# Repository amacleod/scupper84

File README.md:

Scupper84 Row-Staggered Wee Keyboard
=====================================

The Scupper84 is an 84-key (75% layout) row-staggered keyboard in CFX
spacing to be small. The name Scupper is a reference to the Stan
Rogers song [Barrett's Privateers][barretts] which contains the lyric,
"and the cook in the scuppers with the staggers and jags," since this
keyboard uses a row-staggered design.

[barretts]: https://en.wikipedia.org/wiki/Barrett%27s_Privateers

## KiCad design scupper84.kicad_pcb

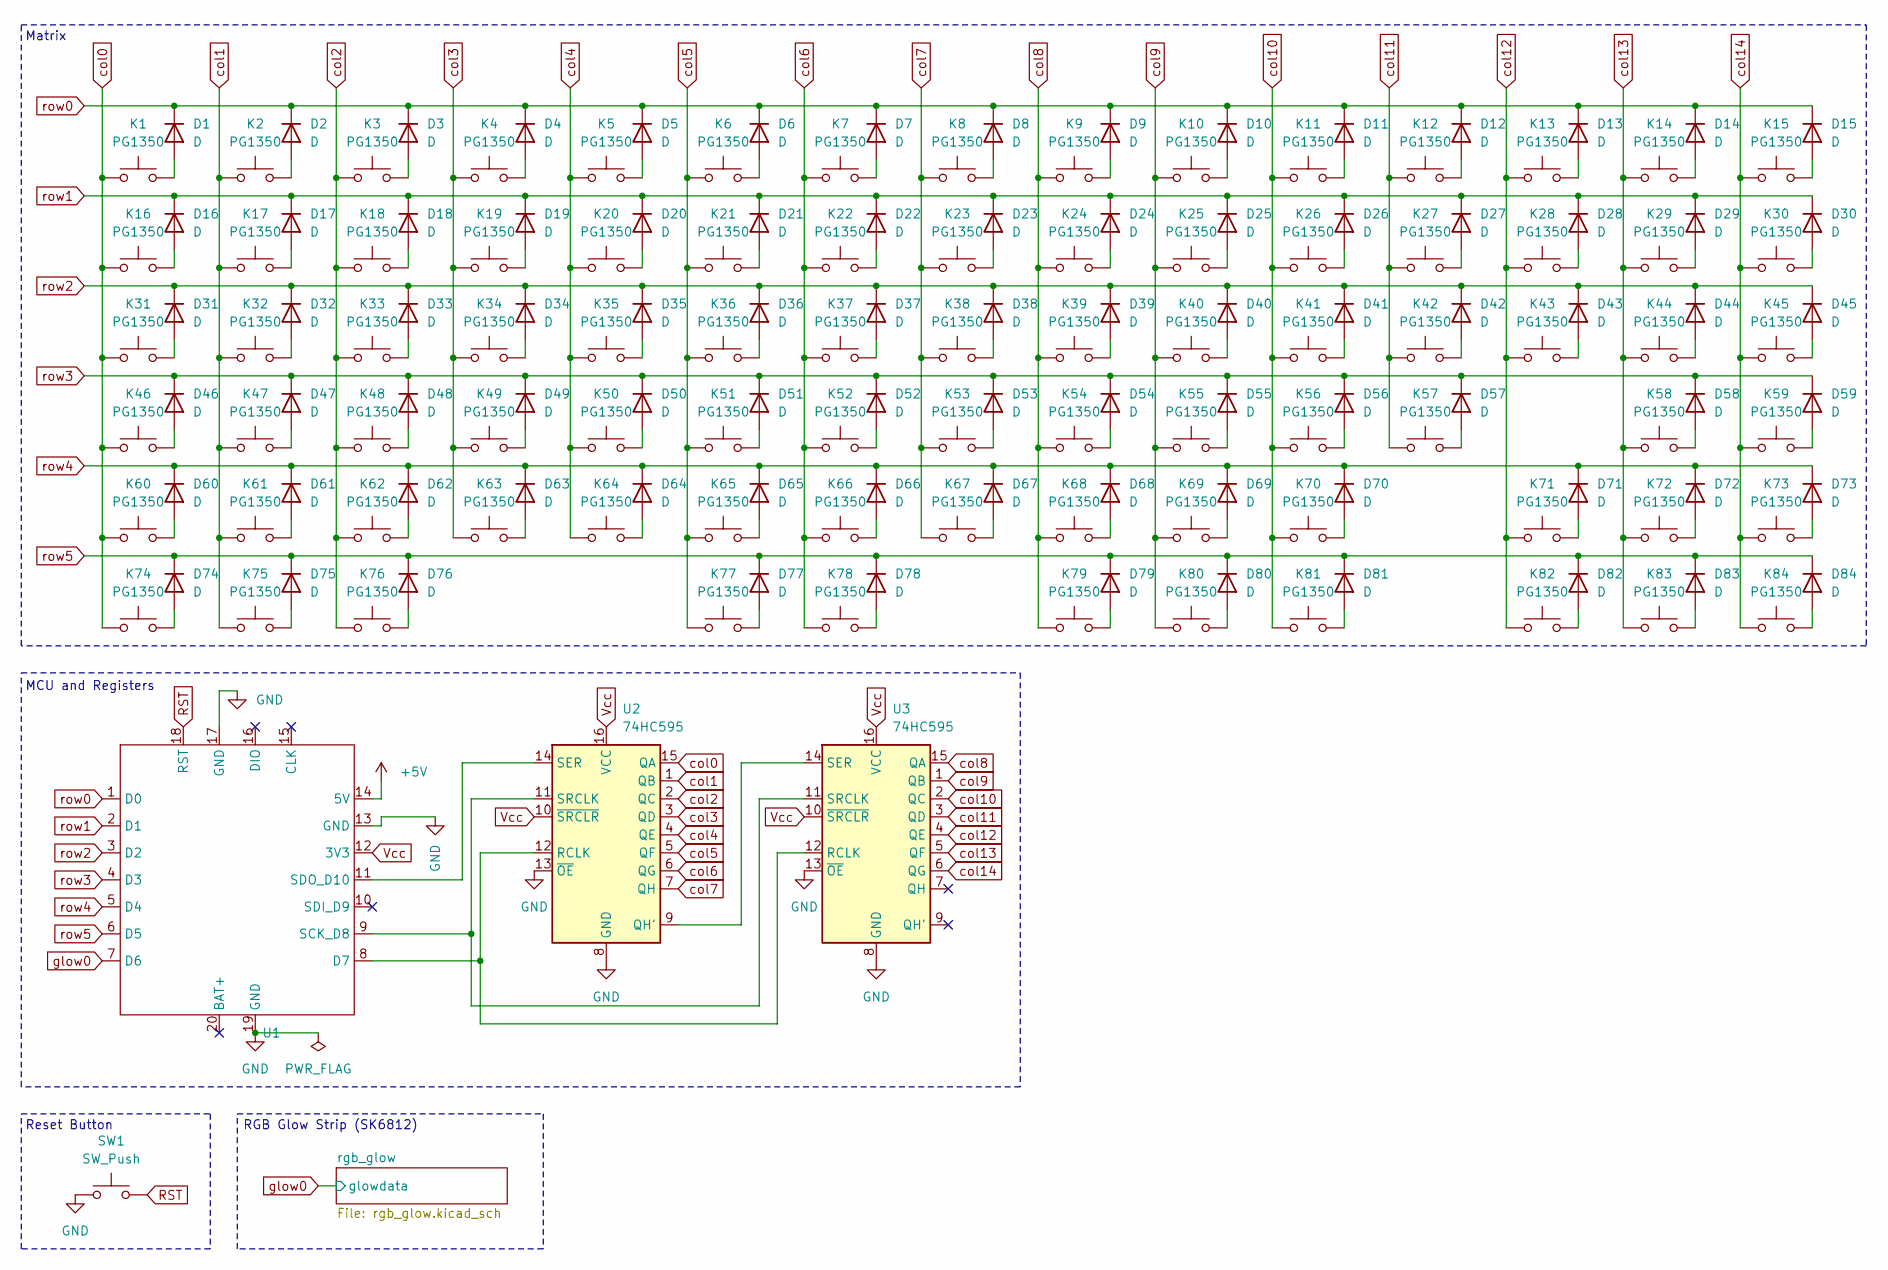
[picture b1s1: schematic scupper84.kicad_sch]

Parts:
D1, D2, D3, D4, D5, D6, D7, D8, D9, D10, D11, D12, D13, D14, D15, D16, D17, D18, D19, D20, D21, D22, D23, D24, D25, D26, D27, D28, D29, D30, D31, D32, D33, D34, D35, D36, D37, D38, D39, D40, D41, D42, D43, D44, D45, D46, D47, D48, D49, D50, D51, D52, D53, D54, D55, D56, D57, D58, D59, D60, D61, D62, D63, D64, D65, D66, D67, D68, D69, D70, D71, D72, D73, D74, D75, D76, D77, D78, D79, D80, D81, D82, D83, D84: D; D_SOD-123
K1, K2, K3, K4, K5, K6, K7, K8, K9, K10, K11, K12, K13, K14, K15, K16, K17, K18, K19, K20, K21, K22, K23, K24, K25, K26, K27, K28, K29, K30, K31, K32, K33, K34, K35, K36, K37, K38, K39, K40, K41, K42, K43, K44, K45, K46, K47, K48, K49, K50, K51, K52, K53, K54, K55, K56, K57, K58, K59, K60, K61, K62, K63, K64, K65, K66, K67, K68, K69, K70, K71, K72, K73, K74, K75, K76, K77, K78, K79, K80, K81, K82, K83, K84: PG1350; Socket_PG1350_Hotswap
SW1: SW_Push; SW_SPST_B3U-1000P
U1: XIAO RP2040 Castellated
U2, U3: 74HC595; SOIC-16_3.9x9.9mm_P1.27mm

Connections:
+5V: U1.14 (5V); also elsewhere on the board
GND: SW1.1, U1.13 (GND), U1.17 (GND), U1.19 (GND), U2.8 (GND), U2.13 (~OE), U3.8 (GND), U3.13 (~OE); also elsewhere on the board
unnamed: D1.2 (A), K1.2
unnamed: D2.2 (A), K2.2
unnamed: D3.2 (A), K3.2
unnamed: D4.2 (A), K4.2
unnamed: D5.2 (A), K5.2
unnamed: D6.2 (A), K6.2
unnamed: D7.2 (A), K7.2
unnamed: D8.2 (A), K8.2
unnamed: D9.2 (A), K9.2
unnamed: D10.2 (A), K10.2
unnamed: D11.2 (A), K11.2
unnamed: D12.2 (A), K12.2
unnamed: D13.2 (A), K13.2
unnamed: D14.2 (A), K14.2
unnamed: D15.2 (A), K15.2
unnamed: D16.2 (A), K16.2
unnamed: D17.2 (A), K17.2
unnamed: D18.2 (A), K18.2
unnamed: D19.2 (A), K19.2
unnamed: D20.2 (A), K20.2
unnamed: D21.2 (A), K21.2
unnamed: D22.2 (A), K22.2
unnamed: D23.2 (A), K23.2
unnamed: D24.2 (A), K24.2
unnamed: D25.2 (A), K25.2
unnamed: D26.2 (A), K26.2
unnamed: D27.2 (A), K27.2
unnamed: D28.2 (A), K28.2
unnamed: D29.2 (A), K29.2
unnamed: D30.2 (A), K30.2
unnamed: D31.2 (A), K31.2
unnamed: D32.2 (A), K32.2
unnamed: D33.2 (A), K33.2
unnamed: D34.2 (A), K34.2
unnamed: D35.2 (A), K35.2
unnamed: D36.2 (A), K36.2
unnamed: D37.2 (A), K37.2
unnamed: D38.2 (A), K38.2
unnamed: D39.2 (A), K39.2
unnamed: D40.2 (A), K40.2
unnamed: D41.2 (A), K41.2
unnamed: D42.2 (A), K42.2
unnamed: D43.2 (A), K43.2
unnamed: D44.2 (A), K44.2
unnamed: D45.2 (A), K45.2
unnamed: D46.2 (A), K46.2
unnamed: D47.2 (A), K47.2
unnamed: D48.2 (A), K48.2
unnamed: D49.2 (A), K49.2
unnamed: D50.2 (A), K50.2
unnamed: D51.2 (A), K51.2
unnamed: D52.2 (A), K52.2
unnamed: D53.2 (A), K53.2
unnamed: D54.2 (A), K54.2
unnamed: D55.2 (A), K55.2
unnamed: D56.2 (A), K56.2
unnamed: D57.2 (A), K57.2
unnamed: D58.2 (A), K58.2
unnamed: D59.2 (A), K59.2
unnamed: D60.2 (A), K60.2
unnamed: D61.2 (A), K61.2
unnamed: D62.2 (A), K62.2
unnamed: D63.2 (A), K63.2
unnamed: D64.2 (A), K64.2
unnamed: D65.2 (A), K65.2
unnamed: D66.2 (A), K66.2
unnamed: D67.2 (A), K67.2
unnamed: D68.2 (A), K68.2
unnamed: D69.2 (A), K69.2
unnamed: D70.2 (A), K70.2
unnamed: D71.2 (A), K71.2
unnamed: D72.2 (A), K72.2
unnamed: D73.2 (A), K73.2
unnamed: D74.2 (A), K74.2
unnamed: D75.2 (A), K75.2
unnamed: D76.2 (A), K76.2
unnamed: D77.2 (A), K77.2
unnamed: D78.2 (A), K78.2
unnamed: D79.2 (A), K79.2
unnamed: D80.2 (A), K80.2
unnamed: D81.2 (A), K81.2
unnamed: D82.2 (A), K82.2
unnamed: D83.2 (A), K83.2
unnamed: D84.2 (A), K84.2
unnamed: U1.8 (D7), U2.12 (RCLK), U3.12 (RCLK)
unnamed: U1.9 (SCK_D8), U2.11 (SRCLK), U3.11 (SRCLK)
unnamed: U1.11 (SDO_D10), U2.14 (SER)
unnamed: U2.9 (QH'), U3.14 (SER)
RST: SW1.2, U1.18 (RST)
Vcc: U1.12 (3V3), U2.10 (~SRCLR), U2.16 (VCC), U3.10 (~SRCLR), U3.16 (VCC)
col0: K1.1, K16.1, K31.1, K46.1, K60.1, K74.1, U2.15 (QA)
col1: K2.1, K17.1, K32.1, K47.1, K61.1, K75.1, U2.1 (QB)
col2: K3.1, K18.1, K33.1, K48.1, K62.1, K76.1, U2.2 (QC)
col3: K4.1, K19.1, K34.1, K49.1, K63.1, U2.3 (QD)
col4: K5.1, K20.1, K35.1, K50.1, K64.1, U2.4 (QE)
col5: K6.1, K21.1, K36.1, K51.1, K65.1, K77.1, U2.5 (QF)
col6: K7.1, K22.1, K37.1, K52.1, K66.1, K78.1, U2.6 (QG)
col7: K8.1, K23.1, K38.1, K53.1, K67.1, U2.7 (QH)
col8: K9.1, K24.1, K39.1, K54.1, K68.1, K79.1, U3.15 (QA)
col9: K10.1, K25.1, K40.1, K55.1, K69.1, K80.1, U3.1 (QB)
col10: K11.1, K26.1, K41.1, K56.1, K70.1, K81.1, U3.2 (QC)
col11: K12.1, K27.1, K42.1, K57.1, U3.3 (QD)
col12: K13.1, K28.1, K43.1, K71.1, K82.1, U3.4 (QE)
col13: K14.1, K29.1, K44.1, K58.1, K72.1, K83.1, U3.5 (QF)
col14: K15.1, K30.1, K45.1, K59.1, K73.1, K84.1, U3.6 (QG)
glow0: U1.7 (D6); also elsewhere on the board
row0: D1.1 (K), D2.1 (K), D3.1 (K), D4.1 (K), D5.1 (K), D6.1 (K), D7.1 (K), D8.1 (K), D9.1 (K), D10.1 (K), D11.1 (K), D12.1 (K), D13.1 (K), D14.1 (K), D15.1 (K), U1.1 (D0)
row1: D16.1 (K), D17.1 (K), D18.1 (K), D19.1 (K), D20.1 (K), D21.1 (K), D22.1 (K), D23.1 (K), D24.1 (K), D25.1 (K), D26.1 (K), D27.1 (K), D28.1 (K), D29.1 (K), D30.1 (K), U1.2 (D1)
row2: D31.1 (K), D32.1 (K), D33.1 (K), D34.1 (K), D35.1 (K), D36.1 (K), D37.1 (K), D38.1 (K), D39.1 (K), D40.1 (K), D41.1 (K), D42.1 (K), D43.1 (K), D44.1 (K), D45.1 (K), U1.3 (D2)
row3: D46.1 (K), D47.1 (K), D48.1 (K), D49.1 (K), D50.1 (K), D51.1 (K), D52.1 (K), D53.1 (K), D54.1 (K), D55.1 (K), D56.1 (K), D57.1 (K), D58.1 (K), D59.1 (K), U1.4 (D3)
row4: D60.1 (K), D61.1 (K), D62.1 (K), D63.1 (K), D64.1 (K), D65.1 (K), D66.1 (K), D67.1 (K), D68.1 (K), D69.1 (K), D70.1 (K), D71.1 (K), D72.1 (K), D73.1 (K), U1.5 (D4)
row5: D74.1 (K), D75.1 (K), D76.1 (K), D77.1 (K), D78.1 (K), D79.1 (K), D80.1 (K), D81.1 (K), D82.1 (K), D83.1 (K), D84.1 (K), U1.6 (D5)

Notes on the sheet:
RGB Glow Strip (SK6812)
Reset Button
MCU and Registers
Matrix

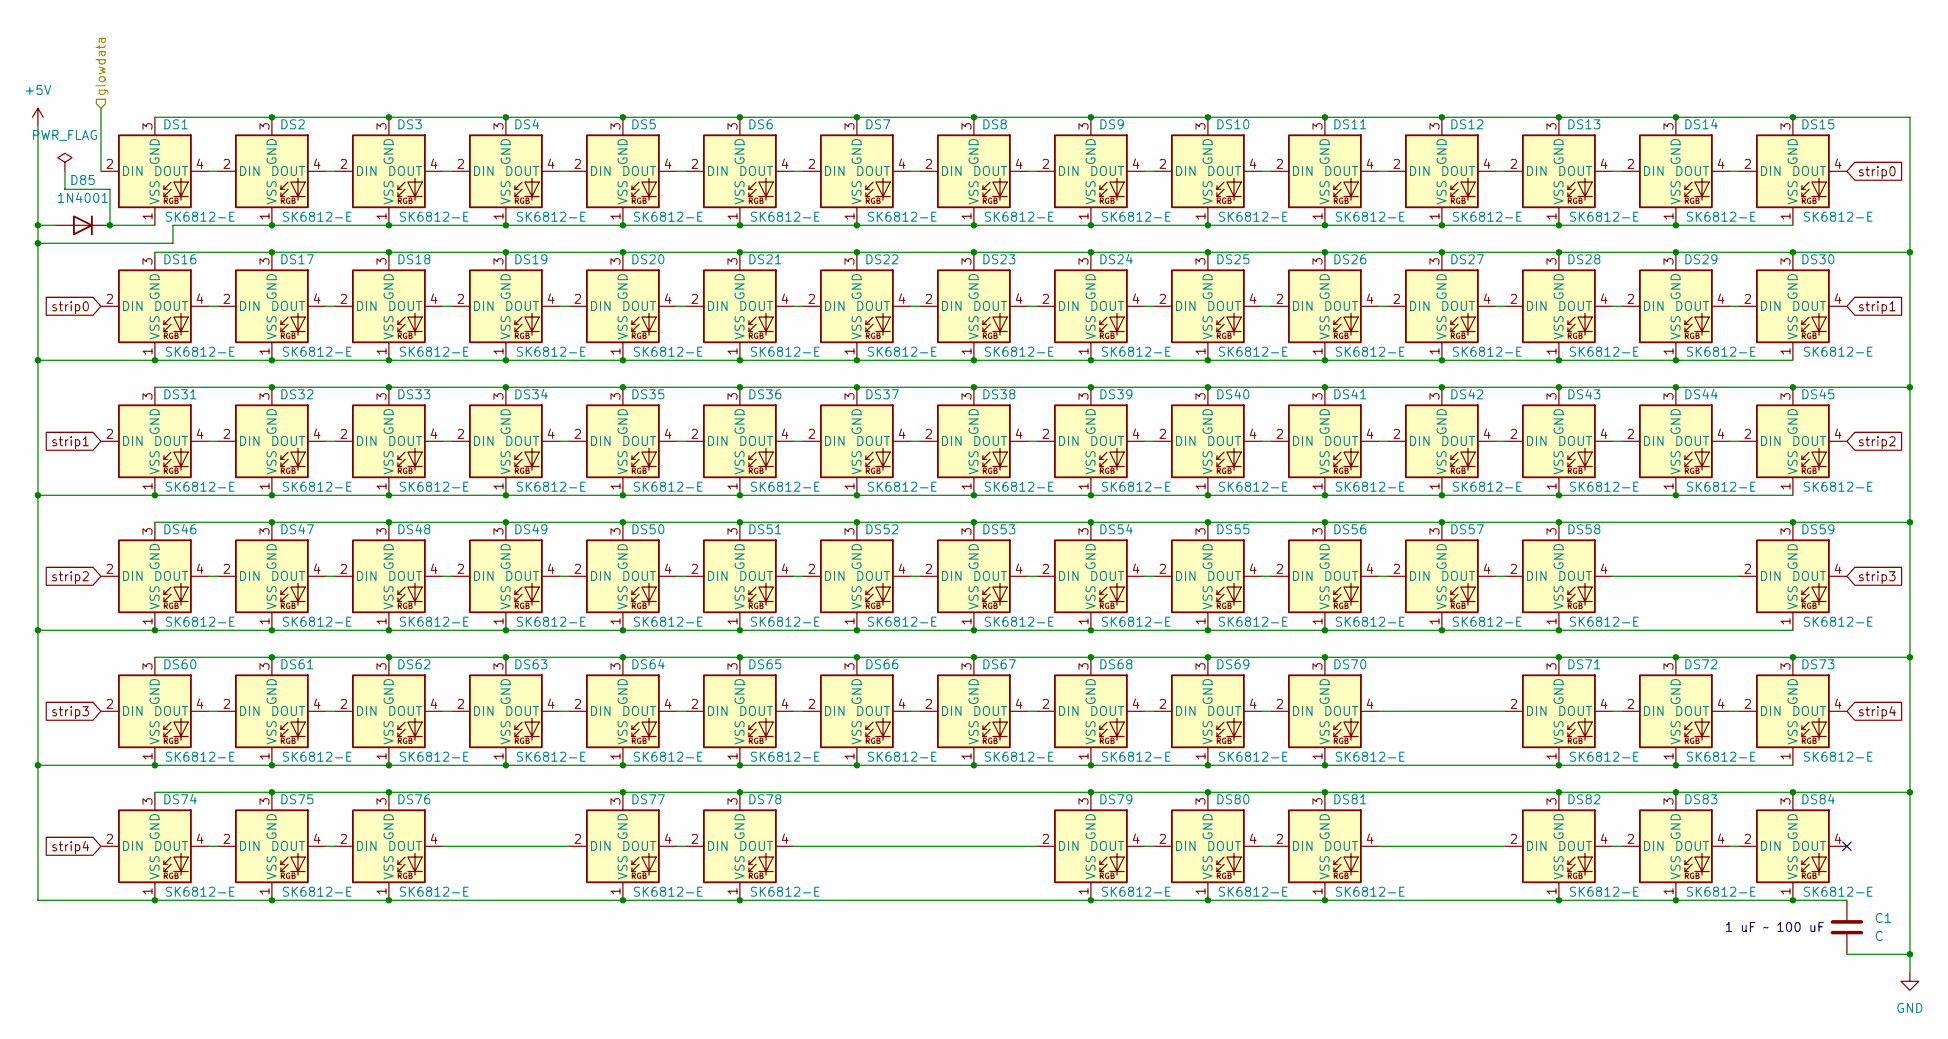
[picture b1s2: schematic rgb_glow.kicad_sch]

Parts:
C1: C; C_1206_3216Metric_Pad1.33x1.80mm_HandSolder
D85: 1N4001; D_DO-41_SOD81_P10.16mm_Horizontal
DS1, DS2, DS3, DS4, DS5, DS6, DS7, DS8, DS9, DS10, DS11, DS12, DS13, DS14, DS15, DS16, DS17, DS18, DS19, DS20, DS21, DS22, DS23, DS24, DS25, DS26, DS27, DS28, DS29, DS30, DS31, DS32, DS33, DS34, DS35, DS36, DS37, DS38, DS39, DS40, DS41, DS42, DS43, DS44, DS45, DS46, DS47, DS48, DS49, DS50, DS51, DS52, DS53, DS54, DS55, DS56, DS57, DS58, DS59, DS60, DS61, DS62, DS63, DS64, DS65, DS66, DS67, DS68, DS69, DS70, DS71, DS72, DS73, DS74, DS75, DS76, DS77, DS78, DS79, DS80, DS81, DS82, DS83, DS84: SK6812-E; LED_RGB_SK6812Mini-E

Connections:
+5V: C1.1, D85.2 (A), DS2.1 (VSS), DS3.1 (VSS), DS4.1 (VSS), DS5.1 (VSS), DS6.1 (VSS), DS7.1 (VSS), DS8.1 (VSS), DS9.1 (VSS), DS10.1 (VSS), DS11.1 (VSS), DS12.1 (VSS), DS13.1 (VSS), DS14.1 (VSS), DS15.1 (VSS), DS16.1 (VSS), DS17.1 (VSS), DS18.1 (VSS), DS19.1 (VSS), DS20.1 (VSS), DS21.1 (VSS), DS22.1 (VSS), DS23.1 (VSS), DS24.1 (VSS), DS25.1 (VSS), DS26.1 (VSS), DS27.1 (VSS), DS28.1 (VSS), DS29.1 (VSS), DS30.1 (VSS), DS31.1 (VSS), DS32.1 (VSS), DS33.1 (VSS), DS34.1 (VSS), DS35.1 (VSS), DS36.1 (VSS), DS37.1 (VSS), DS38.1 (VSS), DS39.1 (VSS), DS40.1 (VSS), DS41.1 (VSS), DS42.1 (VSS), DS43.1 (VSS), DS44.1 (VSS), DS45.1 (VSS), DS46.1 (VSS), DS47.1 (VSS), DS48.1 (VSS), DS49.1 (VSS), DS50.1 (VSS), DS51.1 (VSS), DS52.1 (VSS), DS53.1 (VSS), DS54.1 (VSS), DS55.1 (VSS), DS56.1 (VSS), DS57.1 (VSS), DS58.1 (VSS), DS59.1 (VSS), DS60.1 (VSS), DS61.1 (VSS), DS62.1 (VSS), DS63.1 (VSS), DS64.1 (VSS), DS65.1 (VSS), DS66.1 (VSS), DS67.1 (VSS), DS68.1 (VSS), DS69.1 (VSS), DS70.1 (VSS), DS71.1 (VSS), DS72.1 (VSS), DS73.1 (VSS), DS74.1 (VSS), DS75.1 (VSS), DS76.1 (VSS), DS77.1 (VSS), DS78.1 (VSS), DS79.1 (VSS), DS80.1 (VSS), DS81.1 (VSS), DS82.1 (VSS), DS83.1 (VSS), DS84.1 (VSS); also elsewhere on the board
GND: C1.2, DS1.3 (GND), DS2.3 (GND), DS3.3 (GND), DS4.3 (GND), DS5.3 (GND), DS6.3 (GND), DS7.3 (GND), DS8.3 (GND), DS9.3 (GND), DS10.3 (GND), DS11.3 (GND), DS12.3 (GND), DS13.3 (GND), DS14.3 (GND), DS15.3 (GND), DS16.3 (GND), DS17.3 (GND), DS18.3 (GND), DS19.3 (GND), DS20.3 (GND), DS21.3 (GND), DS22.3 (GND), DS23.3 (GND), DS24.3 (GND), DS25.3 (GND), DS26.3 (GND), DS27.3 (GND), DS28.3 (GND), DS29.3 (GND), DS30.3 (GND), DS31.3 (GND), DS32.3 (GND), DS33.3 (GND), DS34.3 (GND), DS35.3 (GND), DS36.3 (GND), DS37.3 (GND), DS38.3 (GND), DS39.3 (GND), DS40.3 (GND), DS41.3 (GND), DS42.3 (GND), DS43.3 (GND), DS44.3 (GND), DS45.3 (GND), DS46.3 (GND), DS47.3 (GND), DS48.3 (GND), DS49.3 (GND), DS50.3 (GND), DS51.3 (GND), DS52.3 (GND), DS53.3 (GND), DS54.3 (GND), DS55.3 (GND), DS56.3 (GND), DS57.3 (GND), DS58.3 (GND), DS59.3 (GND), DS60.3 (GND), DS61.3 (GND), DS62.3 (GND), DS63.3 (GND), DS64.3 (GND), DS65.3 (GND), DS66.3 (GND), DS67.3 (GND), DS68.3 (GND), DS69.3 (GND), DS70.3 (GND), DS71.3 (GND), DS72.3 (GND), DS73.3 (GND), DS74.3 (GND), DS75.3 (GND), DS76.3 (GND), DS77.3 (GND), DS78.3 (GND), DS79.3 (GND), DS80.3 (GND), DS81.3 (GND), DS82.3 (GND), DS83.3 (GND), DS84.3 (GND); also elsewhere on the board
unnamed: D85.1 (K), DS1.1 (VSS)
unnamed: DS1.4 (DOUT), DS2.2 (DIN)
unnamed: DS2.4 (DOUT), DS3.2 (DIN)
unnamed: DS3.4 (DOUT), DS4.2 (DIN)
unnamed: DS4.4 (DOUT), DS5.2 (DIN)
unnamed: DS5.4 (DOUT), DS6.2 (DIN)
unnamed: DS6.4 (DOUT), DS7.2 (DIN)
unnamed: DS7.4 (DOUT), DS8.2 (DIN)
unnamed: DS8.4 (DOUT), DS9.2 (DIN)
unnamed: DS9.4 (DOUT), DS10.2 (DIN)
unnamed: DS10.4 (DOUT), DS11.2 (DIN)
unnamed: DS11.4 (DOUT), DS12.2 (DIN)
unnamed: DS12.4 (DOUT), DS13.2 (DIN)
unnamed: DS13.4 (DOUT), DS14.2 (DIN)
unnamed: DS14.4 (DOUT), DS15.2 (DIN)
unnamed: DS16.4 (DOUT), DS17.2 (DIN)
unnamed: DS17.4 (DOUT), DS18.2 (DIN)
unnamed: DS18.4 (DOUT), DS19.2 (DIN)
unnamed: DS19.4 (DOUT), DS20.2 (DIN)
unnamed: DS20.4 (DOUT), DS21.2 (DIN)
unnamed: DS21.4 (DOUT), DS22.2 (DIN)
unnamed: DS22.4 (DOUT), DS23.2 (DIN)
unnamed: DS23.4 (DOUT), DS24.2 (DIN)
unnamed: DS24.4 (DOUT), DS25.2 (DIN)
unnamed: DS25.4 (DOUT), DS26.2 (DIN)
unnamed: DS26.4 (DOUT), DS27.2 (DIN)
unnamed: DS27.4 (DOUT), DS28.2 (DIN)
unnamed: DS28.4 (DOUT), DS29.2 (DIN)
unnamed: DS29.4 (DOUT), DS30.2 (DIN)
unnamed: DS31.4 (DOUT), DS32.2 (DIN)
unnamed: DS32.4 (DOUT), DS33.2 (DIN)
unnamed: DS33.4 (DOUT), DS34.2 (DIN)
unnamed: DS34.4 (DOUT), DS35.2 (DIN)
unnamed: DS35.4 (DOUT), DS36.2 (DIN)
unnamed: DS36.4 (DOUT), DS37.2 (DIN)
unnamed: DS37.4 (DOUT), DS38.2 (DIN)
unnamed: DS38.4 (DOUT), DS39.2 (DIN)
unnamed: DS39.4 (DOUT), DS40.2 (DIN)
unnamed: DS40.4 (DOUT), DS41.2 (DIN)
unnamed: DS41.4 (DOUT), DS42.2 (DIN)
unnamed: DS42.4 (DOUT), DS43.2 (DIN)
unnamed: DS43.4 (DOUT), DS44.2 (DIN)
unnamed: DS44.4 (DOUT), DS45.2 (DIN)
unnamed: DS46.4 (DOUT), DS47.2 (DIN)
unnamed: DS47.4 (DOUT), DS48.2 (DIN)
unnamed: DS48.4 (DOUT), DS49.2 (DIN)
unnamed: DS49.4 (DOUT), DS50.2 (DIN)
unnamed: DS50.4 (DOUT), DS51.2 (DIN)
unnamed: DS51.4 (DOUT), DS52.2 (DIN)
unnamed: DS52.4 (DOUT), DS53.2 (DIN)
unnamed: DS53.4 (DOUT), DS54.2 (DIN)
unnamed: DS54.4 (DOUT), DS55.2 (DIN)
unnamed: DS55.4 (DOUT), DS56.2 (DIN)
unnamed: DS56.4 (DOUT), DS57.2 (DIN)
unnamed: DS57.4 (DOUT), DS58.2 (DIN)
unnamed: DS58.4 (DOUT), DS59.2 (DIN)
unnamed: DS60.4 (DOUT), DS61.2 (DIN)
unnamed: DS61.4 (DOUT), DS62.2 (DIN)
unnamed: DS62.4 (DOUT), DS63.2 (DIN)
unnamed: DS63.4 (DOUT), DS64.2 (DIN)
unnamed: DS64.4 (DOUT), DS65.2 (DIN)
unnamed: DS65.4 (DOUT), DS66.2 (DIN)
unnamed: DS66.4 (DOUT), DS67.2 (DIN)
unnamed: DS67.4 (DOUT), DS68.2 (DIN)
unnamed: DS68.4 (DOUT), DS69.2 (DIN)
unnamed: DS69.4 (DOUT), DS70.2 (DIN)
unnamed: DS70.4 (DOUT), DS71.2 (DIN)
unnamed: DS71.4 (DOUT), DS72.2 (DIN)
unnamed: DS72.4 (DOUT), DS73.2 (DIN)
unnamed: DS74.4 (DOUT), DS75.2 (DIN)
unnamed: DS75.4 (DOUT), DS76.2 (DIN)
unnamed: DS76.4 (DOUT), DS77.2 (DIN)
unnamed: DS77.4 (DOUT), DS78.2 (DIN)
unnamed: DS78.4 (DOUT), DS79.2 (DIN)
unnamed: DS79.4 (DOUT), DS80.2 (DIN)
unnamed: DS80.4 (DOUT), DS81.2 (DIN)
unnamed: DS81.4 (DOUT), DS82.2 (DIN)
unnamed: DS82.4 (DOUT), DS83.2 (DIN)
unnamed: DS83.4 (DOUT), DS84.2 (DIN)
glow0: DS1.2 (DIN); also elsewhere on the board
strip0: DS15.4 (DOUT), DS16.2 (DIN)
strip1: DS30.4 (DOUT), DS31.2 (DIN)
strip2: DS45.4 (DOUT), DS46.2 (DIN)
strip3: DS59.4 (DOUT), DS60.2 (DIN)
strip4: DS73.4 (DOUT), DS74.2 (DIN)

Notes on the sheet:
1 uF ~ 100 uF

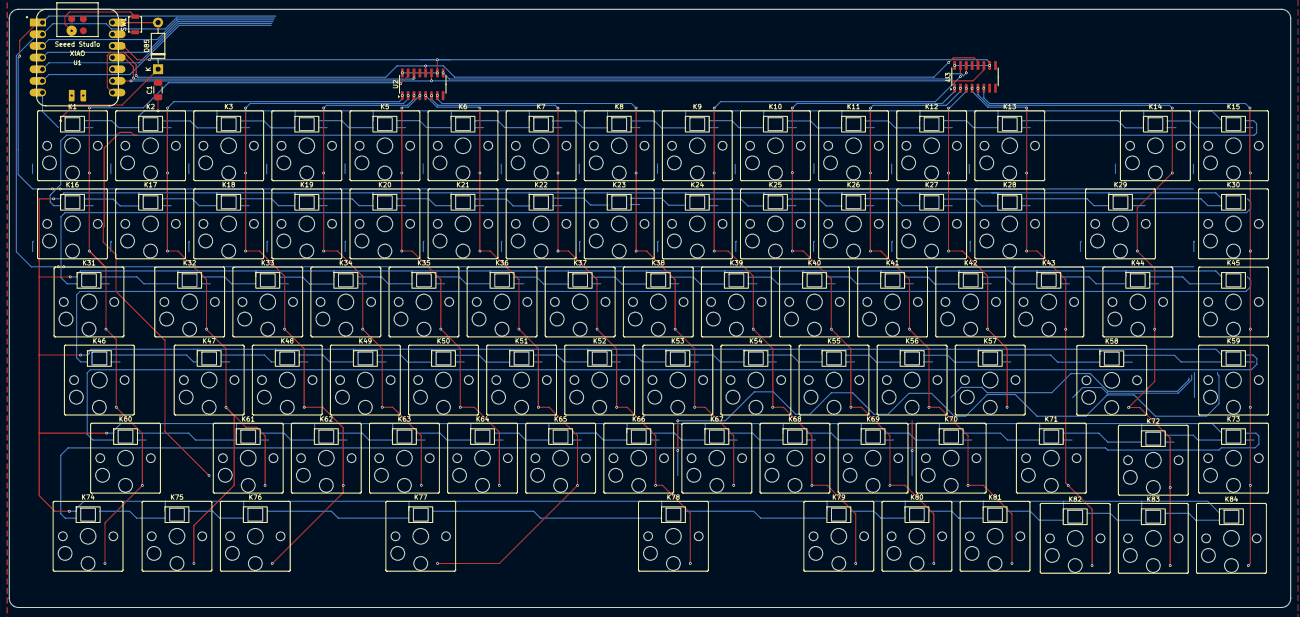
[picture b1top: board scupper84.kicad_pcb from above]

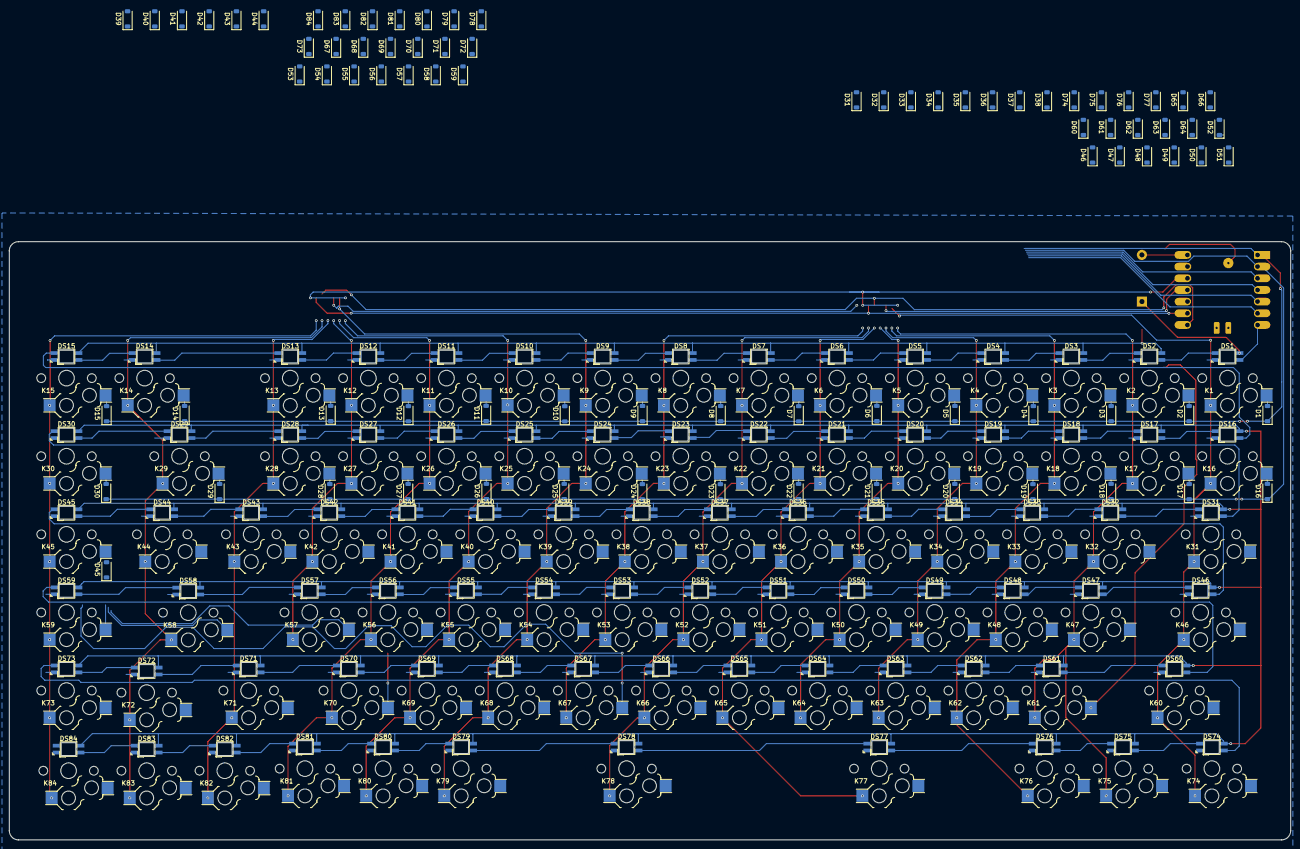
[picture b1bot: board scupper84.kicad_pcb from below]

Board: 2 copper layers, 278.9 x 130.2 mm, 258 parts (84 on the bottom side), 198 nets.

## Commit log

2024-10-13 First stab at some Ergogen.
2024-10-21 Copying stuff into the repo.
2024-11-03 Custom keyboard parts for Scupper84
2024-11-03 Symbol library
2024-11-03 Initial schematic for Scupper84
2024-11-03 Adding power flag to satisfy ERC.
2024-11-03 Footprint for XIAO RP2040
2024-11-04 Drop rat's nest on PCB.
2024-11-16 Work in progress on Kailh footprints.
2024-11-16 Changing footprints to use my new Kailh socket footprint.
2024-11-17 Arranging keys in their staggered array. Keys bigger than 1u may still need some adjustment.
2024-11-17 Repositioning RGB LEDs with a script.
2024-11-17 Provisionally placing shift registers and stuff. I should position them precisely before planning any builds.
2024-11-19 Messing around with keycap placement.
2024-11-19 Centering switches under keycaps that moved.
2024-11-19 Arranging diodes.
2024-11-19 Repositioning LEDs after moving keyswitches.
2024-12-06 WIP routing key matrix.
2024-12-07 Trying a different way of routing row traces.
2024-12-07 Fiddling with routing a lot, trying the controller in the northwest corner.
2024-12-07 Trying a rule of vertical stuff on the front layer and horizontal stuff on the back layer.
2024-12-08 More rerouting.
2024-12-08 Rotating GND labels to point down.
2024-12-08 Starting the diode row-return routing.
2024-12-09 Moving diodes to the back of the board.
2024-12-22 Routing the rest of the rows and placing the diodes on the back side.
2025-02-26 Some additions to the global parts library: RP2040 Zero and KB2040 Kee Boar.
2025-12-27 Fix link for Barrett's Privateers page on Wikipedia.
